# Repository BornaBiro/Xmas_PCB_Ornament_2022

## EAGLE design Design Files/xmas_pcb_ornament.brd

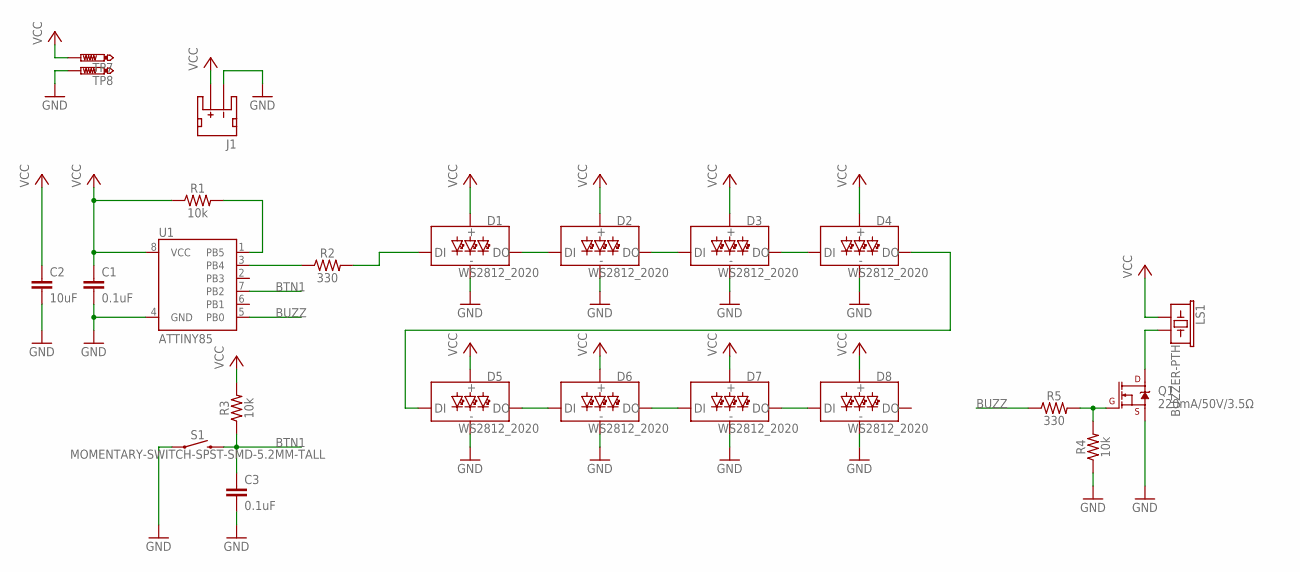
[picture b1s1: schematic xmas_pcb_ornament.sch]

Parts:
C1, C3: 0.1uF; 0603
C2: 10uF; 1206
D1, D2, D3, D4, D5, D6, D7, D8: WS2812_2020; WS2812-2020
J1: JST_2MM_MALE; JST-2-SMD
LS1: BUZZER-PTH; BUZZER-12MM
Q1: 220mA/50V/3.5Ω; SOT23-3
R1, R3, R4: 10k; 0603
R2, R5: 330; 0603
S1: MOMENTARY-SWITCH-SPST-SMD-5.2MM-TALL; TACTILE_SWITCH_SMD_5.2MM
TP7, TP8: PTR1TP20R; TP20R
U1: ATTINY85

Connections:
BTN1: C3.1, R3.1, S1.3 (2), S1.4 (2), U1.7 (PB2)
BUZZ: R5.1, U1.5 (PB0)
GND: C1.2, C2.2, C3.2, D1.GND, D2.GND, D3.GND, D4.GND, D5.GND, D6.GND, D7.GND, D8.GND, J1.1 (-), Q1.2 (S), R4.1, S1.1, S1.2 (1), TP8.TP, U1.4 (GND)
unnamed: Q1.1 (G), R4.2, R5.2
unnamed: LS1.- (2), Q1.3 (D)
unnamed: R1.2, U1.1 (PB5)
unnamed: R2.1, U1.3 (PB4)
unnamed: D1.DI, R2.2
unnamed: D1.DO, D2.DI
unnamed: D2.DO, D3.DI
unnamed: D3.DO, D4.DI
unnamed: D4.DO, D5.DI
unnamed: D5.DO, D6.DI
unnamed: D6.DO, D7.DI
unnamed: D7.DO, D8.DI
VCC: C1.1, C2.1, D1.VCC, D2.VCC, D3.VCC, D4.VCC, D5.VCC, D6.VCC, D7.VCC, D8.VCC, J1.2 (+), LS1.+ (1), R1.1, R3.2, TP7.TP, U1.8 (VCC)

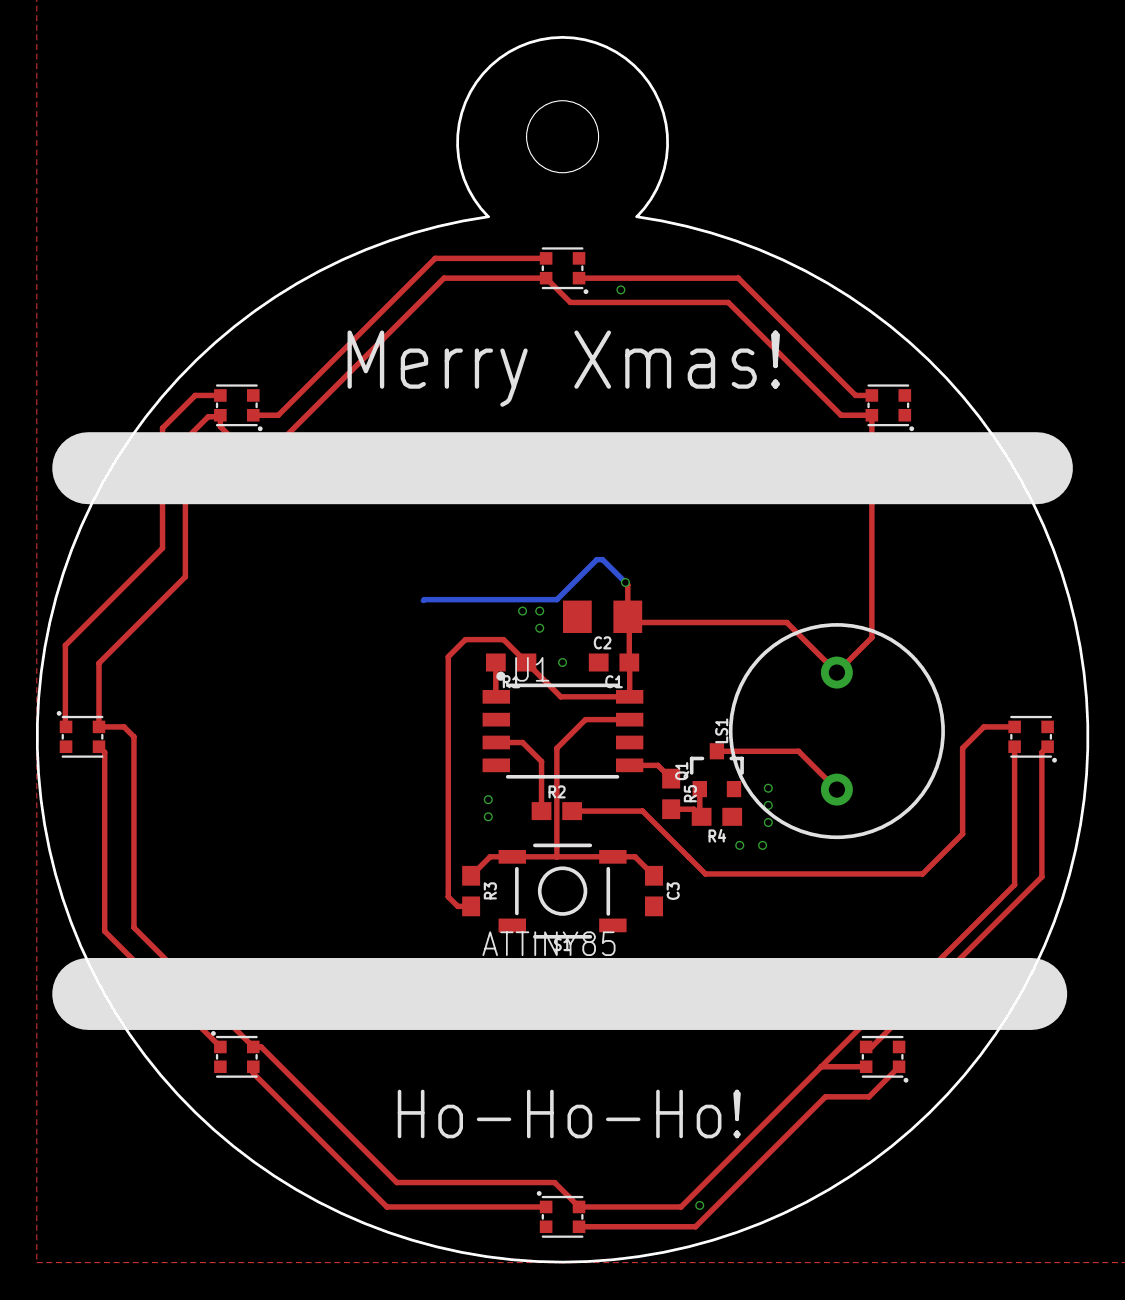
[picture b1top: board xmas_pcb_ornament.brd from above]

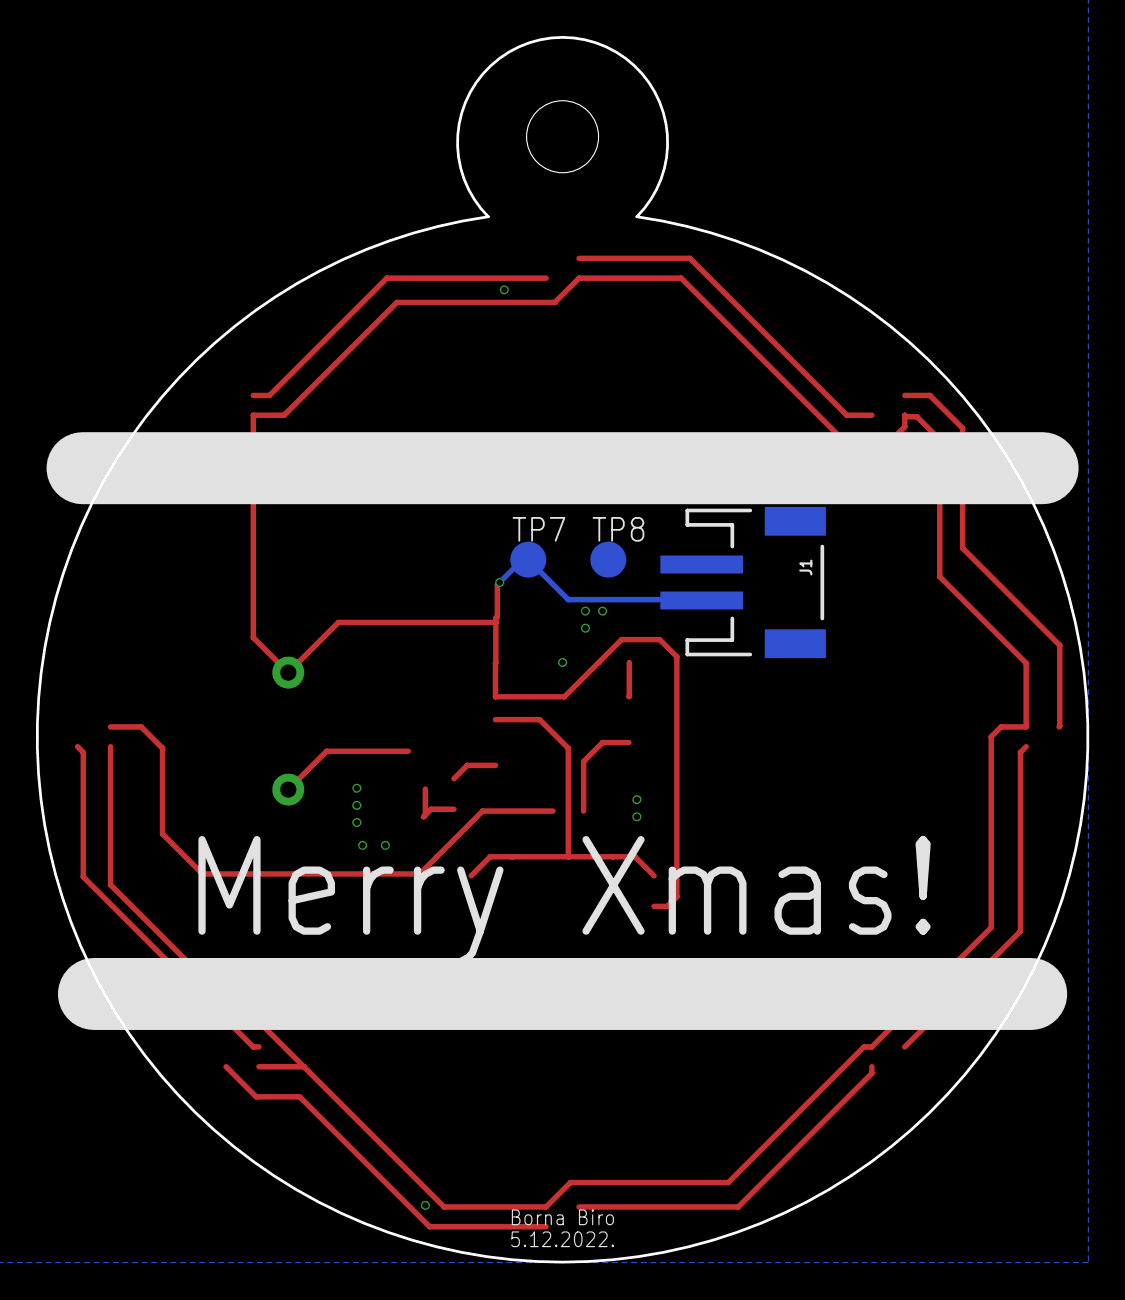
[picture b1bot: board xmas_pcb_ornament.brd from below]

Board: 2 copper layers, 58.4 x 68.0 mm, 23 parts (3 on the bottom side), 16 nets.

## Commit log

2022-12-05 Added PCB files.
2022-12-05 Changed placement of the stripes and JST connector.
2022-12-05 Changed position of the text on the back.
2022-12-07 More design changes.
2022-12-26 Added FW.

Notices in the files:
parts and their libraries:
SparkFun-Capacitors: Licensing: Creative Commons ShareAlike 4.0 International - https://creativecommons.org/licenses/by-sa/4.0
